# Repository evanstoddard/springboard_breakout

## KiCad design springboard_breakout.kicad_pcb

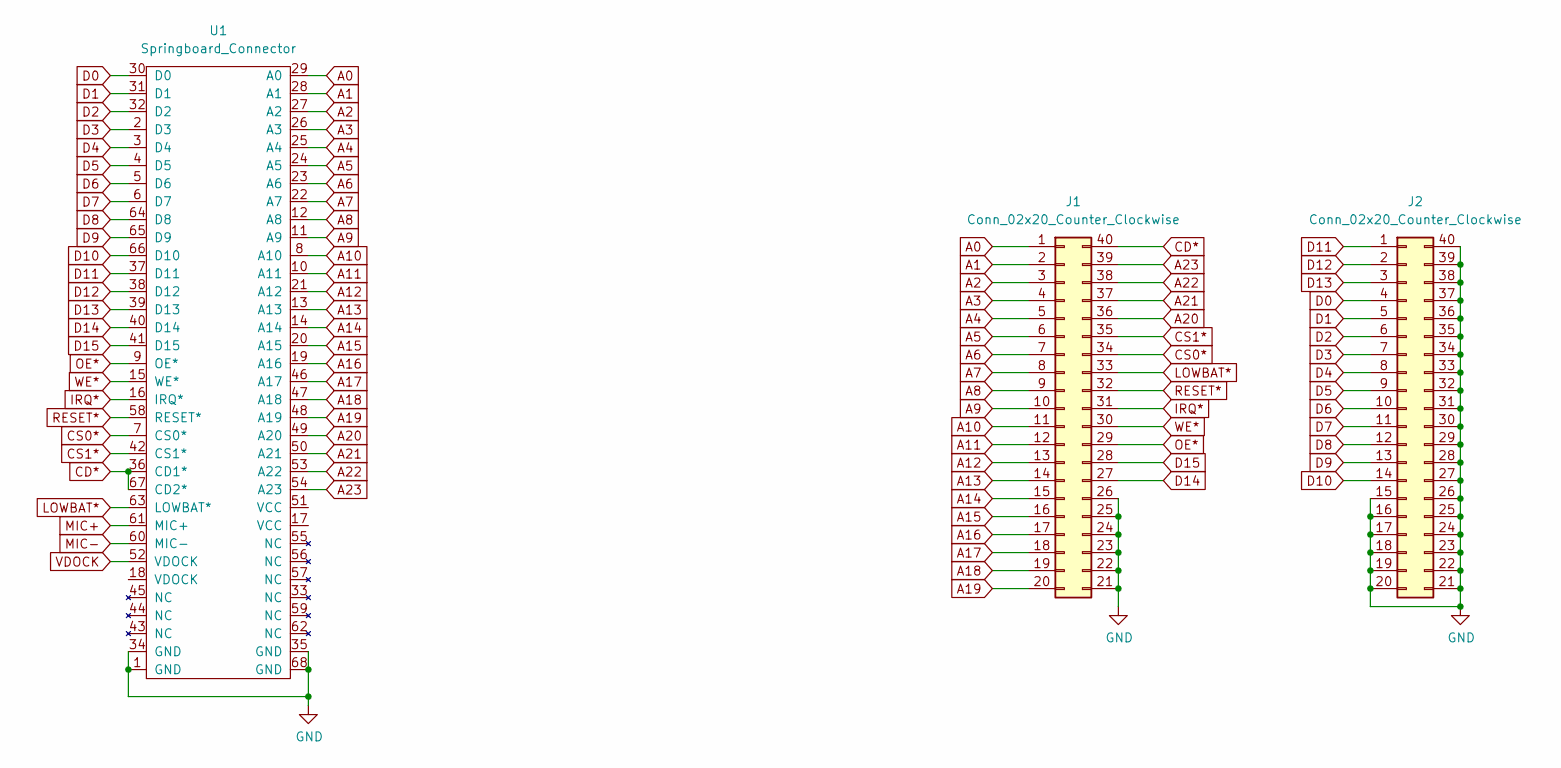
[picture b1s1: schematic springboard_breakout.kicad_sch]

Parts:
J1, J2: Conn_02x20_Counter_Clockwise; PinHeader_2x20_P2.00mm_Vertical
U1: Springboard_Connector; Springboard Connector

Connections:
A0: J1.1, U1.29 (A0)
A1: J1.2, U1.28 (A1)
A2: J1.3, U1.27 (A2)
A3: J1.4, U1.26 (A3)
A4: J1.5, U1.25 (A4)
A5: J1.6, U1.24 (A5)
A6: J1.7, U1.23 (A6)
A7: J1.8, U1.22 (A7)
A8: J1.9, U1.12 (A8)
A9: J1.10, U1.11 (A9)
A10: J1.11, U1.8 (A10)
A11: J1.12, U1.10 (A11)
A12: J1.13, U1.21 (A12)
A13: J1.14, U1.13 (A13)
A14: J1.15, U1.14 (A14)
A15: J1.16, U1.20 (A15)
A16: J1.17, U1.19 (A16)
A17: J1.18, U1.46 (A17)
A18: J1.19, U1.47 (A18)
A19: J1.20, U1.48 (A19)
A20: J1.36, U1.49 (A20)
A21: J1.37, U1.50 (A21)
A22: J1.38, U1.53 (A22)
A23: J1.39, U1.54 (A23)
CD*: J1.40, U1.36 (CD1*), U1.67 (CD2*)
CS0*: J1.34, U1.7 (CS0*)
CS1*: J1.35, U1.42 (CS1*)
D0: J2.4, U1.30 (D0)
D1: J2.5, U1.31 (D1)
D2: J2.6, U1.32 (D2)
D3: J2.7, U1.2 (D3)
D4: J2.8, U1.3 (D4)
D5: J2.9, U1.4 (D5)
D6: J2.10, U1.5 (D6)
D7: J2.11, U1.6 (D7)
D8: J2.12, U1.64 (D8)
D9: J2.13, U1.65 (D9)
D10: J2.14, U1.66 (D10)
D11: J2.1, U1.37 (D11)
D12: J2.2, U1.38 (D12)
D13: J2.3, U1.39 (D13)
D14: J1.27, U1.40 (D14)
D15: J1.28, U1.41 (D15)
GND: J1.21, J1.22, J1.23, J1.24, J1.25, J1.26, J2.15, J2.16, J2.17, J2.18, J2.19, J2.20, J2.21, J2.22, J2.23, J2.24, J2.25, J2.26, J2.27, J2.28, J2.29, J2.30, J2.31, J2.32, J2.33, J2.34, J2.35, J2.36, J2.37, J2.38, J2.39, J2.40, U1.1 (GND), U1.34 (GND), U1.35 (GND), U1.68 (GND)
IRQ*: J1.31, U1.16 (IRQ*)
LOWBAT*: J1.33, U1.63 (LOWBAT*)
MIC+: U1.61 (MIC+)
MIC-: U1.60 (MIC-)
OE*: J1.29, U1.9 (OE*)
RESET*: J1.32, U1.58 (RESET*)
VDOCK: U1.52 (VDOCK)
WE*: J1.30, U1.15 (WE*)

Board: 2 copper layers, 3 parts (0 on the bottom side), 49 nets, no tracks yet.

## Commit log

2022-09-19 Updated 40 pin header footprint to 2.00 mm pitch
